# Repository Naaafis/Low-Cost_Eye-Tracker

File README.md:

Demo Video -> https://youtu.be/nrKnskTpATE

# Low-Cost_Eye-Tracker
Development of eye tracking software that can be used to control digital systems without the use of hands. 

Notable software files:

tracker_flask: API directory

tracker_flask/trackerAPI/app.py: api source file

eye_tracker.ipynb: notebook displaying the funcitonalities of the eye tracker

To launch API:

```
cd tracker_flask
pip install pipenv
pipenv shell
pipenv install
./bootstrap.sh
```

The PCB was devloped in Eagle and hold the following components.
- ESP32-S2-Saola
- MAX7219
- Arudcam Mini
- 1088AS LED Matrix

It utilized SPI to communicate across all the devices and HTTP to interact with the cloud application. The ESP is loaded with the program in the Arduino IDE and used the arducam mini pc host application to send the command to capture an image.

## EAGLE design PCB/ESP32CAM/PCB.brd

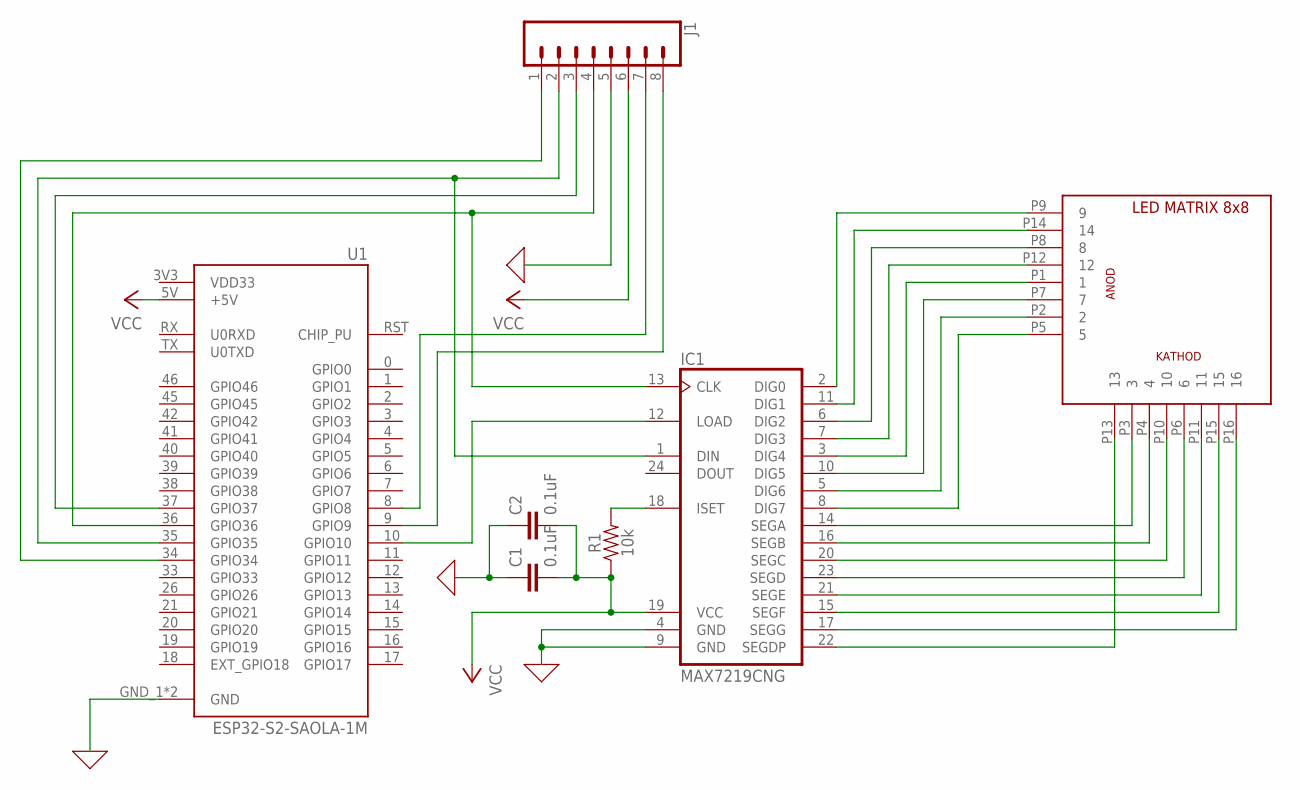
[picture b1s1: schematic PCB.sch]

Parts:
C1, C2: 0.1uF; CAP-PTH-SMALL-KIT
IC1: MAX7219CNG; DIL24-3
J1: CONN_08"; 1X08
R1: 10k; AXIAL-0.3
U1: ESP32-S2-SAOLA-1M; MODULE_ESP32-S2-SAOLA-1M
U$2: LEDMAT8X8THROUGH_HOLE; LEDMAT8X8

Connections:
0: C1.1, C2.1, IC1.4 (GND), IC1.9 (GND), J1.5, U1.GND_1 (GND), U1.GND_2 (GND)
unnamed: J1.1, U1.34 (GPIO34)
unnamed: IC1.1 (DIN), J1.2, U1.35 (GPIO35)
unnamed: J1.3, U1.37 (GPIO37)
unnamed: IC1.13 (CLK), J1.4, U1.36 (GPIO36)
unnamed: J1.7, U1.8 (GPIO8)
unnamed: IC1.2 (DIG0), U$2.P9 (9)
unnamed: IC1.11 (DIG1), U$2.P14 (14)
unnamed: IC1.6 (DIG2), U$2.P8 (8)
unnamed: IC1.7 (DIG3), U$2.P12 (12)
unnamed: IC1.3 (DIG4), U$2.P1 (1)
unnamed: IC1.10 (DIG5), U$2.P7 (7)
unnamed: IC1.5 (DIG6), U$2.P2 (2)
unnamed: IC1.8 (DIG7), U$2.P5 (5)
unnamed: IC1.22 (SEGDP), U$2.P13 (13)
unnamed: IC1.14 (SEGA), U$2.P3 (3)
unnamed: IC1.16 (SEGB), U$2.P4 (4)
unnamed: IC1.20 (SEGC), U$2.P10 (10)
unnamed: IC1.23 (SEGD), U$2.P6 (6)
unnamed: IC1.21 (SEGE), U$2.P11 (11)
unnamed: IC1.15 (SEGF), U$2.P15 (15)
unnamed: IC1.17 (SEGG), U$2.P16 (16)
unnamed: J1.8, U1.9 (GPIO9)
unnamed: IC1.18 (ISET), R1.P$2 (2)
unnamed: IC1.12 (LOAD), U1.10 (GPIO10)
VCC: C1.2, C2.2, IC1.19 (VCC), J1.6, R1.P$1 (1), U1.5V (+5V)
VDD33: U1.3V3 (VDD33)

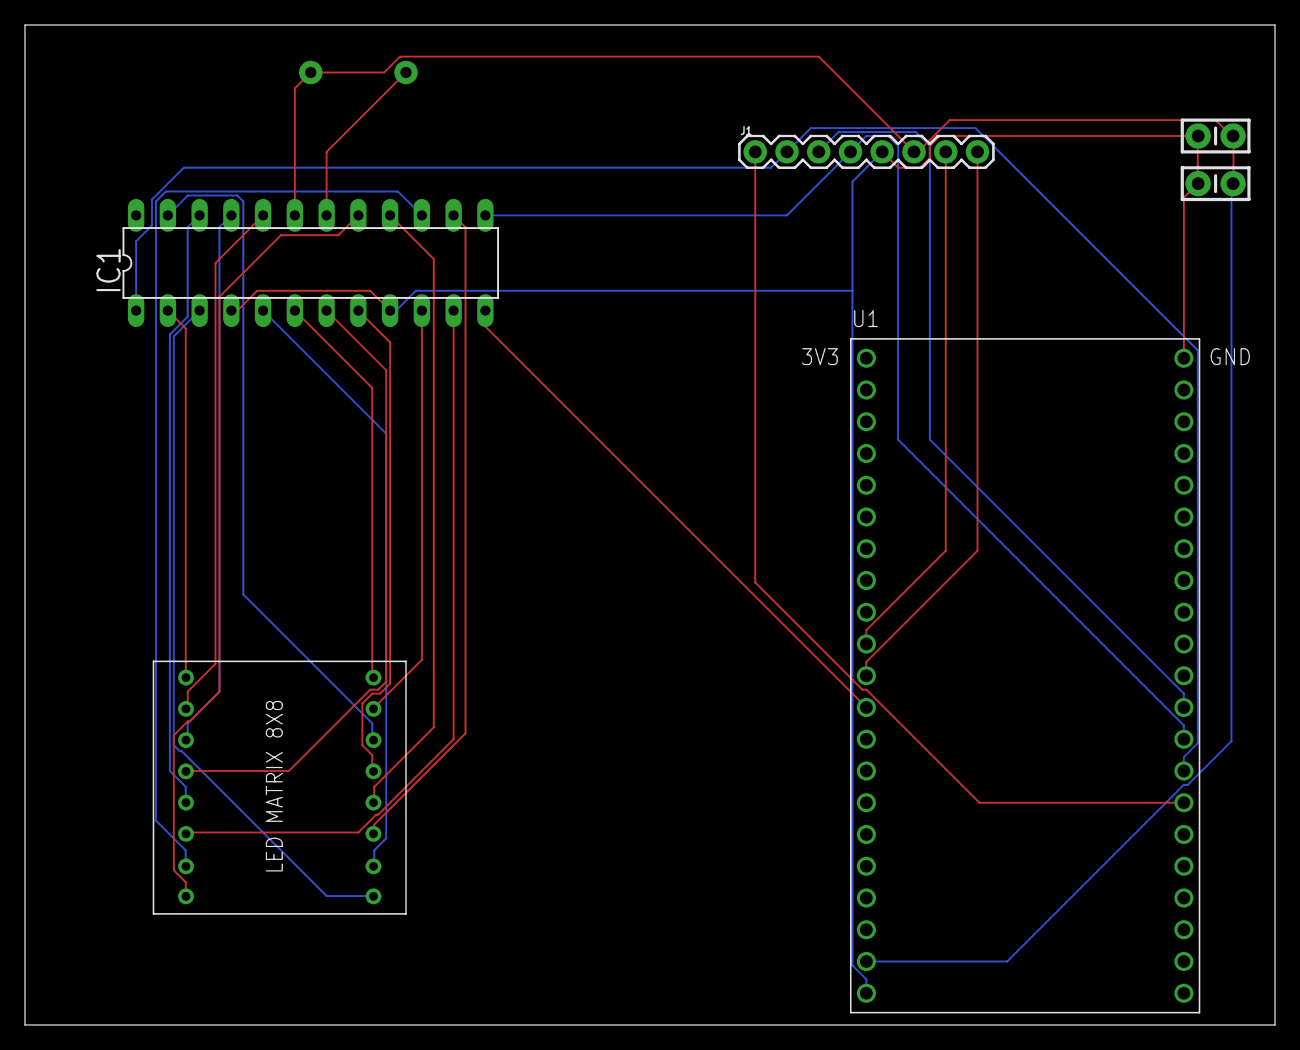
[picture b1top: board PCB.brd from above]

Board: 2 copper layers, 100.0 x 80.0 mm, 7 parts (1 on the bottom side), 26 nets.

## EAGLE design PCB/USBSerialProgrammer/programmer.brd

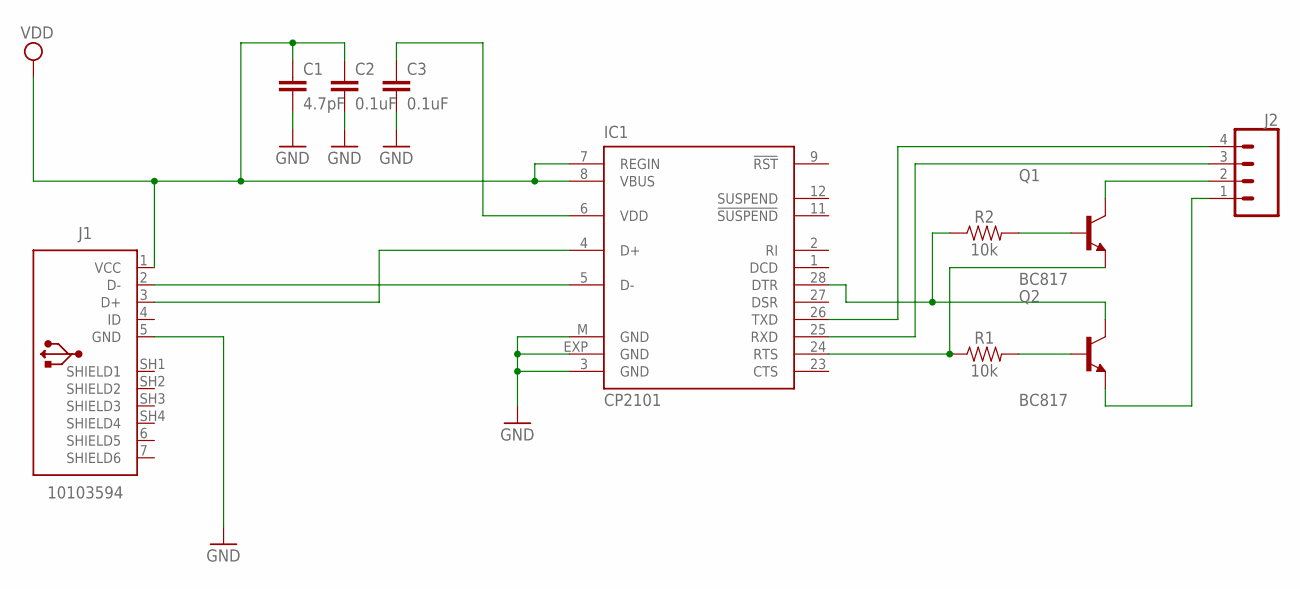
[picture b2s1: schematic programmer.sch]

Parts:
C1: 4.7pF; 0603
C2, C3: 0.1uF; 0402
IC1: CP2101; MLP28
J1: 10103594
J2: CONN_04; 1X04
Q1, Q2: BC817; SOT95P230X110-3N
R1, R2: 10k; AXIAL-0.3

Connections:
GND: C1.2, C2.2, C3.2, IC1.3 (GND), IC1.EXP (GND), IC1.M (GND), J1.5 (GND)
unnamed: IC1.5 (D-), J1.2 (D-)
unnamed: IC1.4 (D+), J1.3 (D+)
unnamed: IC1.25 (RXD), J2.3
unnamed: IC1.26 (TXD), J2.4
unnamed: C3.1, IC1.6 (VDD)
unnamed: J2.2, Q1.3 (C)
unnamed: IC1.28 (DTR), Q2.3 (C), R2.P$1 (1)
unnamed: J2.1, Q2.2 (E)
unnamed: IC1.24 (RTS), Q1.2 (E), R1.P$1 (1)
unnamed: Q2.1 (B), R1.P$2 (2)
unnamed: Q1.1 (B), R2.P$2 (2)
VDD: C1.1, C2.1, IC1.7 (REGIN), IC1.8 (VBUS), J1.1 (VCC)

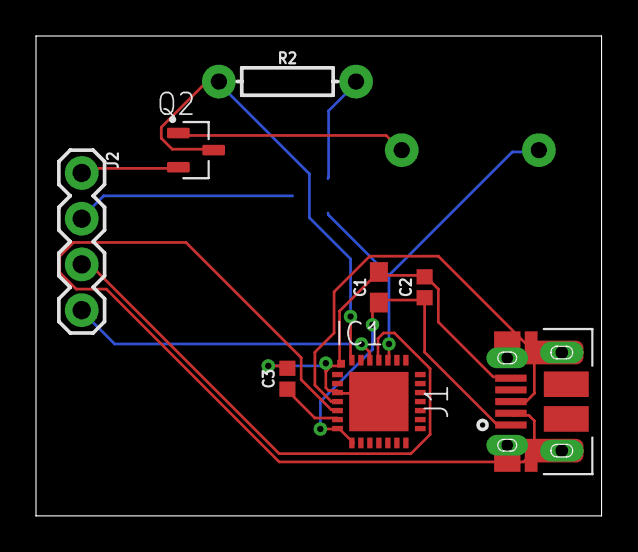
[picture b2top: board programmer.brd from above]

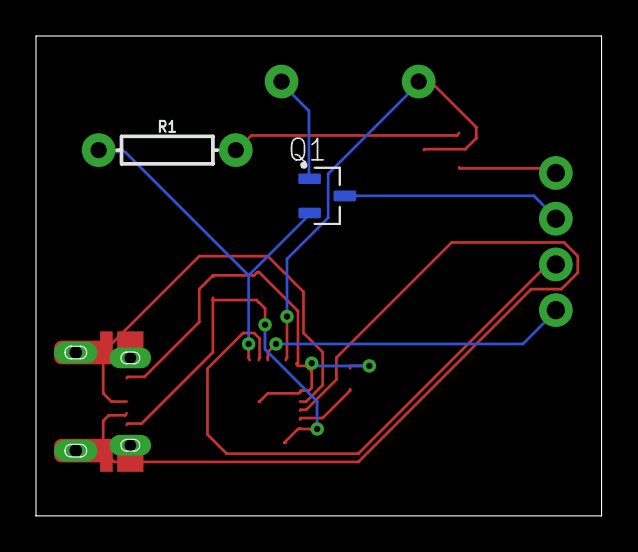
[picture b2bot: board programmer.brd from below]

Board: 2 copper layers, 31.4 x 26.7 mm, 10 parts (2 on the bottom side), 13 nets.

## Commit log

2023-03-10 initializations
2023-03-10 Updated report for easy commands view
2023-03-10 updated to .md file
2023-03-10 Rename week_1_log.txt to week_1_log.md
2023-03-10 Added all library installation commands
2023-03-24 week 2 logs
2023-03-24 added edited python file
2023-03-28 basic face and eye detection
2023-03-28 added source
2023-04-03 ESP Code and USB Programmer PCB
2023-04-11 displays
2023-04-12 isolate eyes
2023-04-12 blob detection
2023-04-12 attempting to get circles to show up on webcam images
2023-04-24 PCB Design
2023-04-24 updated PDF
2023-05-01 opencv_sol
2023-05-01 tested eye tracker function for left, right, center on base64encoded images from the ESP
2023-05-01 added simple flask app to display API funcitionality
2023-05-03 working API
2023-05-03 Final esp code

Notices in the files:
parts and their libraries:
SparkFun-Connectors: Licensing: Creative Commons ShareAlike 4.0 International - https://creativecommons.org/licenses/by-sa/4.0
